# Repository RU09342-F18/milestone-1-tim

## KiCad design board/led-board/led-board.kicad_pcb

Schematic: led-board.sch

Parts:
C1: 22uF; CP_Radial_D5.0mm_P2.50mm
C2: 0.1uF; C_Disc_D3.0mm_W1.6mm_P2.50mm
D1: LED_ARGB; LED_D5.0mm-4_RGB
J1: UART_In; PinHeader_1x02_P2.54mm_Horizontal
J2: Pwr_In; PinHeader_1x02_P2.54mm_Horizontal
J3: Pwr_Out; PinSocket_1x02_P2.54mm_Horizontal
J4: UART_Out; PinSocket_1x02_P2.54mm_Horizontal
J5: Pgrm; PinHeader_1x02_P2.54mm_Vertical
Q1, Q2, Q3: 2N7000; TO-92_Inline
R1: 10k; R_Axial_DIN0207_L6.3mm_D2.5mm_P7.62mm_Horizontal
R2, R4, R6: 1M; R_Axial_DIN0207_L6.3mm_D2.5mm_P7.62mm_Horizontal
R3, R5, R7: 470; R_Axial_DIN0207_L6.3mm_D2.5mm_P7.62mm_Horizontal
U1: L78L33_TO92; TO-92_Inline
U2: MSP430G2553IN20; DIP-20_W7.62mm

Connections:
+3V3: C2.1, R1.1, U1.1 (VO), U2.1 (DVCC)
+5V: C1.1, D1.2, J2.1, J3.1, U1.3 (VI)
/BLUE: Q3.2, R6.1, U2.14 (TDI/TCLK/UCB0SOMI/UCB0SCL/TA0.1/CA6/A6/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)
/GREEN: Q2.2, R4.1, U2.12 (P2.4/TA1.2)
/RED: Q1.2, R2.1, U2.9 (P2.1/TA1.1)
/RESET: J5.2, R1.2, U2.16 (~RST~/NMI/SBWTDIO)
/RX: J1.1, U2.3 (UCA0RXD/UCA0SOMI/TA0.0/CA1/A1/P1.1)
/TEST: J5.1, U2.17 (TEST/SBWTCK)
/TX: J4.1, U2.4 (UCA0TXD/UCA0SIMO/TA0.1/CA2/A2/P1.2)
GND: C1.2, C2.2, J2.2, J3.2, Q1.1, Q2.1, Q3.1, R2.2, R4.2, R6.2, U1.2 (GND), U2.20 (DVSS)
unnamed: D1.1, R3.1
unnamed: D1.3, R5.1
unnamed: D1.4, R7.1
unnamed: J1.2, J4.2
unnamed: Q1.3, R3.2
unnamed: Q2.3, R5.2
unnamed: Q3.3, R7.2

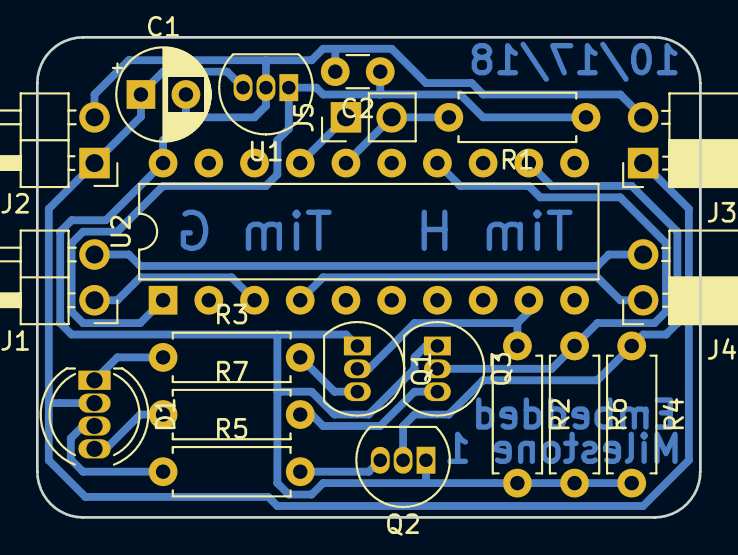
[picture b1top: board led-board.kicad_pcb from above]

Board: 2 copper layers, 36.8 x 26.7 mm, 20 parts (0 on the bottom side), 17 nets.

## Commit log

2018-10-10 add uart example
2018-10-17 last attempt at g2 with external resonator
2018-10-19 Use multiple timers on g2
2018-10-19 add board files
